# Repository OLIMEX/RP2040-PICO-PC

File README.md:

# RP2040-PICO-PC
Board of peripherals for Raspberry Pi RP2040-PICO which adds:

- HDMI/DVI 
- Audio 
- Micro SD card 
- Li-po charger 
- UEXT
- USB-OTG 

Allows to create a small PC with monitor and keyboard.

The RP2040-PICO-PC design is Open-Source Hardware (OSHW).

## Licenses

* Hardware is released under CERN Open Hardware Licence Version 2 - Strongly Reciprocal, all silkscreen credits to Olimex should remain;
* Software is released under GPL3 Licensee
* Documentation is released under CC BY-SA 4.0

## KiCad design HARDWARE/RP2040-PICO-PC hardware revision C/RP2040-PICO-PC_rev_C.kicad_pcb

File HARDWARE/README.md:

RP2040-PICO-PC HARDWARE

This folder conaints design source files for each major hardware revisions.

There are also PDF exports of the schematic and BOM exports available.

The designs are made with KiCAD. Below you can find revision changes:

====

- Hardware revision D

1. Con2 changed to qwst1 and pinout changed!
2. Imropoved the pads and the soldering of all bigger components. They should now be more sturdy.

====

- Hardware revision C

1. Added diode D1 at the HDMI connector. R6 changed to 27k.
2. I2C1 fixed. SCL and SDA were swapped at the processor (3.3V).
3. Added needed resistors and capacitors and ferrite beads to SD_Card.
4. Board size increased.

====

- Hardware revision B

Initial release.

====

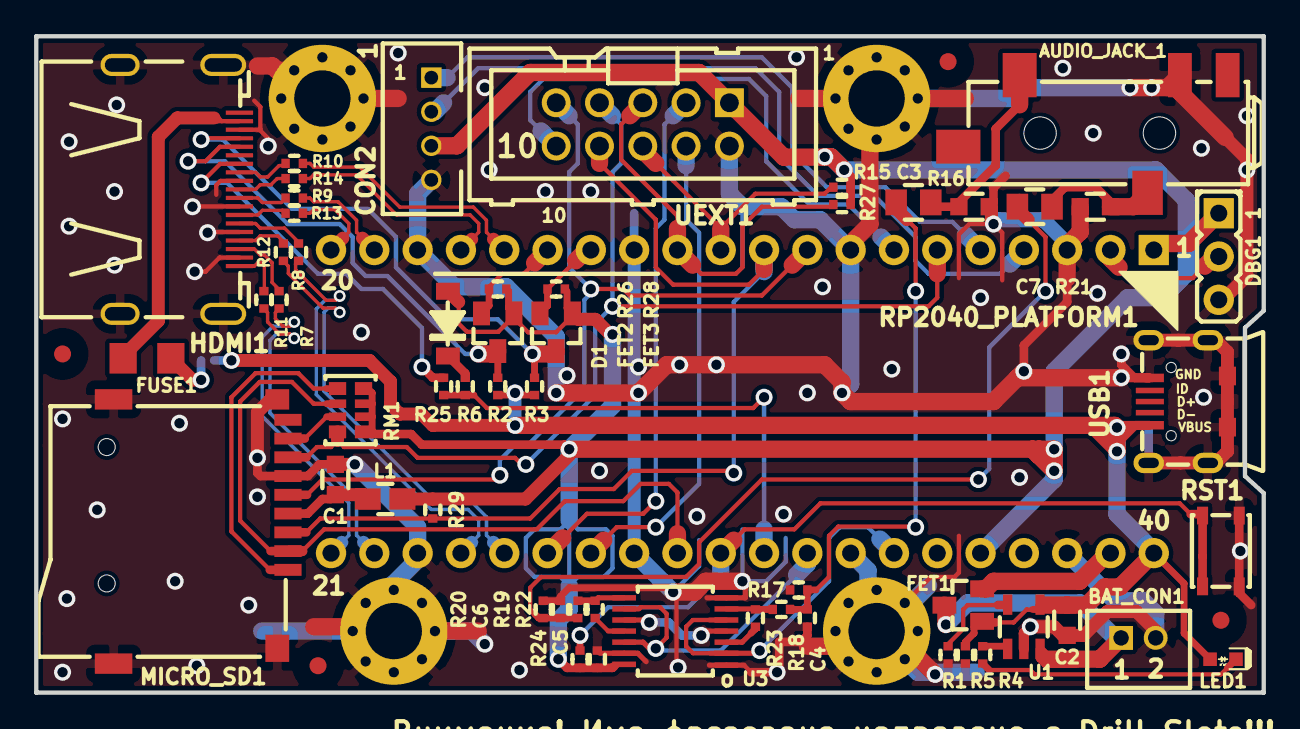
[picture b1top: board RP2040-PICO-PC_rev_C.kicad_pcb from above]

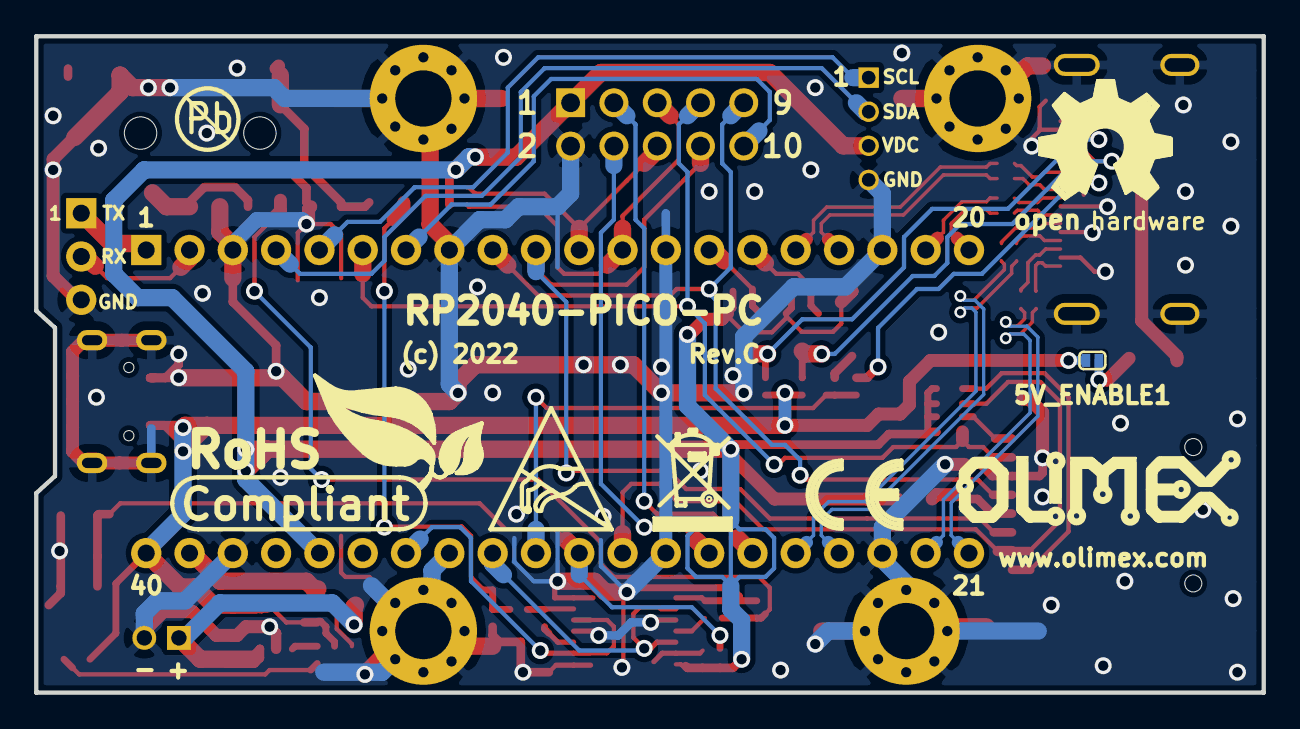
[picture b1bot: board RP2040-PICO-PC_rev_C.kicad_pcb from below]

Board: 2 copper layers, 72.0 x 38.5 mm, 71 parts (7 on the bottom side), 60 nets.

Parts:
5V_ENABLE1: open; SJ_1_SMALLER
AUDIO_JACK_1: 3.5mm PJ-W47S-05D2-LF; PJ-W47S-05D2-LF_5PIN_V2
Antistatic: Logo; LOGO_ANTISTATIC_1
BAT_CON1: DW02S; LIPO_BAT_VERTICAL_DW02S
C1: 0603 10 UF 6.3V; C_0603_5MIL_DWS
C2: 0603 1 UF 10V 10% X5R; C_0603_5MIL_DWS
C3, C7: 0805 47 UF 6.3V 20% X5R; C_0805_5MIL_DWS
C4, C5, C6: 0402 100 NF 10V 20% X5R; C_0402_5MIL_DWS
CON2: CI0104P1VK0 (PH-4A); CL0104PV1K0
D1: 1N5819 (S4 SOD-123); SOD-123_1C-2A_KA
DBG1: HN1x3
FET1: WPM2015-3/TR; SOT23
FET2, FET3: BSS138; SOT23
FID1, FID2, FID3, FID4: Fiducial; Fiducial1x3
FUSE1: FSMD035-1206 (NANOSMDC035F-2); FUSE-1206
HDMI1: HDMI-SWM-19
L1: 0805 600 OHM 2A HIGH CURRENT; L_0805_5MIL_DWS
LED1: LED 0603 RED 300 mCd; LED_0603_KA
MH1, MH2, MH3, MH4: Mounting_hole_Shield_3.3mm
MICRO_SD1: TFC-WPAPR-08-LF; TFC-WPAPR-08
OLIMEX_LOGO: Logo; OLIMEX_LOGO_TB
Open_Hardware: Logo; LOGO_OPENHARDWARE_8x8
PB_FREE: Logo; LOGO_PBFREE
R1: 0402 1.5 K 5%; R_0402_5MIL_DWS
R2, R3, R15, R26, R27, R28: 0402 2.2 K 5%; R_0402_5MIL_DWS
R4: 0402 2 K 5%; R_0402_5MIL_DWS
R5: 0402 100 K 5%; R_0402_5MIL_DWS
R6: 0402 27 K 5%; R_0402_5MIL_DWS
R7, R8, R9, R10, R11, R12, R13, R14, R25: 0402 270 OHM 5%; R_0402_5MIL_DWS
R16, R21: 0603 1.8 K 5%; R_0603_5MIL_DWS
R17, R20: 0402 100 OHM 5%; R_0402_5MIL_DWS
R18, R19: 0402 220 OHM 5%; R_0402_5MIL_DWS
R22, R23: NA/0402; R_0402_5MIL_DWS
R24, R29: 0402 10 K 5%; R_0402_5MIL_DWS
RM1: RMAT (4x0603) 100 K 5%; RA1206_(4X0603)_4B8_xx
RP2040_PLATFORM1: 2X(PN1X20(F-D-1X20-LF)); RP_Pico2040
RST1: YTS-A016-X
Recycle_bin: logo; LOGO_RECYCLEBIN_1
RoHS_Complaint: Logo; LOGO_ROHS_1
U1: BL4054B-42TPRN; SOT-23-5
U3: 74LVC125APW; 74LVC125A(TSSOP14-14_leads-4.4mm_body_width-SOT402-1)
UEXT1: BH10S (B-D-02x5-LF); BH10S
USB1: MISB-SWMM-5B-LF; USB-MICRO_MISB-SWMM-5B_LF

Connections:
+3V3: C5.1, CON2.3, D1.2, FET2.1, FET3.1, L1.1, R15.1, R24.1, R26.2, R27.2, R28.2, R29.2, RM1.1.1, RM1.2.1, RM1.3.1, RM1.4.1, RP2040_PLATFORM1.36, U3.14, UEXT1.1
+5V: 5V_ENABLE1.1, C2.2, FET1.1, LED1.2, R2.1, R3.1, R5.2, RP2040_PLATFORM1.40, U1.4, USB1.1
+BATT: BAT_CON1.1, FET1.3, U1.3
/CK+: HDMI1.10, R14.2
/CK-: HDMI1.12, R10.2
/D0+: HDMI1.7, R13.2
/D0-: HDMI1.9, R9.2
/D1+: HDMI1.4, R12.2
/D1-: HDMI1.6, R8.2
/D2+: HDMI1.1, R11.2
/D2-: HDMI1.3, R7.2
/DVI_CEC: R6.2, R25.1, RP2040_PLATFORM1.31
/I2C0_SCL: R27.1, RP2040_PLATFORM1.12, UEXT1.5
/I2C0_SDA: R15.2, RP2040_PLATFORM1.11, UEXT1.6
/I2C1A_SCL_5: FET2.3, HDMI1.15, R2.2
/I2C1A_SCL_33: FET2.2, R26.1, RP2040_PLATFORM1.15
/I2C1A_SDA_5: FET3.3, HDMI1.16, R3.2
/I2C1A_SDA_33: FET3.2, R28.1, RP2040_PLATFORM1.14
/I2C1_SCL: CON2.1, RP2040_PLATFORM1.5
/I2C1_SDA: CON2.2, RP2040_PLATFORM1.4
/PICO_CK+: R14.1, RP2040_PLATFORM1.17
/PICO_CK-: R10.1, RP2040_PLATFORM1.16
/PICO_D0+: R13.1, RP2040_PLATFORM1.20
/PICO_D0-: R9.1, RP2040_PLATFORM1.19
/PICO_D1+: R12.1, RP2040_PLATFORM1.25
/PICO_D1-: R8.1, RP2040_PLATFORM1.24
/PICO_D2+: R11.1, RP2040_PLATFORM1.22
/PICO_D2-: R7.1, RP2040_PLATFORM1.21
/PWM_AUDIO_L: AUDIO_JACK_1.2, C3.1, R16.2
/PWM_AUDIO_R: AUDIO_JACK_1.3, C7.1, R21.2
/PWM_L: RP2040_PLATFORM1.34, U3.2, U3.5
/PWM_R: RP2040_PLATFORM1.32, U3.9, U3.12
/SPI0_CLK: MICRO_SD1.5, RP2040_PLATFORM1.9, UEXT1.9
/SPI0_CSn0: RP2040_PLATFORM1.7, UEXT1.10
/SPI0_CSn1: MICRO_SD1.2, RM1.3.2, RP2040_PLATFORM1.29
/SPI0_MISO: MICRO_SD1.7, RM1.1.2, RP2040_PLATFORM1.6, UEXT1.7
/SPI0_MOSI: MICRO_SD1.3, R29.1, RP2040_PLATFORM1.10, UEXT1.8
/UART0_RX: DBG1.2, RP2040_PLATFORM1.2
/UART0_TX: DBG1.1, RP2040_PLATFORM1.1
/UART1_RX: RP2040_PLATFORM1.27, UEXT1.4
/UART1_TX: RP2040_PLATFORM1.26, UEXT1.3
/VSYS: FET1.2, RP2040_PLATFORM1.39
/nRESET: R24.2, RP2040_PLATFORM1.30, RST1.1
GND: AUDIO_JACK_1.5, BAT_CON1.2, C1.1, C2.1, C4.1, C5.2, C6.1, CON2.4, DBG1.3, HDMI1.0, HDMI1.2, HDMI1.5, HDMI1.8, HDMI1.11, HDMI1.17, MH1.GND1, MH2.GND1, MH3.GND1, MH4.GND1, MICRO_SD1.6, MICRO_SD1.10, MICRO_SD1.11, MICRO_SD1.12, MICRO_SD1.13, R1.2, R5.1, R16.1, R17.1, R20.1, R21.1, RP2040_PLATFORM1.3, RP2040_PLATFORM1.8, RP2040_PLATFORM1.13, RP2040_PLATFORM1.18, RP2040_PLATFORM1.23, RP2040_PLATFORM1.28, RP2040_PLATFORM1.33, RP2040_PLATFORM1.38, RST1.2, U1.2, U3.1, U3.4, U3.7, U3.10, U3.13, UEXT1.2, USB1.0, USB1.5
unnamed: 5V_ENABLE1.2, FUSE1.1
unnamed: C1.2, L1.2, MICRO_SD1.4
unnamed: C3.2, C4.2, R17.2, R18.1
unnamed: C6.2, C7.2, R19.1, R20.2
unnamed: D1.1, R6.1
unnamed: FUSE1.2, HDMI1.18
unnamed: HDMI1.13, R25.2
unnamed: LED1.1, R4.2
unnamed: MICRO_SD1.1, RM1.4.2
unnamed: MICRO_SD1.8, RM1.2.2
unnamed: R1.1, U1.5
unnamed: R4.1, U1.1
unnamed: R18.2, R23.1, U3.6
unnamed: R19.2, R22.1, U3.8
unnamed: R22.2, U3.11
unnamed: R23.2, U3.3

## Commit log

2022-11-02 Update
    Added hardware
2022-11-08 Software examples
    Added software examples
2025-03-31 Update
    Revision C and D and revision changes

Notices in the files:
HARDWARE/RP2040-PICO-PC hardware revision C/RP2040-PICO-PC_rev_C.kicad_pcb:
(c) 2022
